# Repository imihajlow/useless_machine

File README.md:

# Useless machine

This project is an attempt to design a useless machine (the one that does nothing but turing off the switch) from scratch.
The reductor gears are designed to be 3d-printed.
The low-power controller can be reused for other small applications: it provides some GPIO pins, UART, and bidirectional motor driver.
The controller's power consumption is low enough to sustain on a CR2032 battery for more than 1.5 years in standby mode.

* mechanics/ - AutoCAD drawings of the mechanical part of the machine. This folder also contains the belt length calculation script.
* controller/ - the electronic part. Schematic drawing, PCB layout and gerber files for production.
* firmware/ - firmware for the controller. You need SDCC (http://sdcc.sourceforge.net) to compile.

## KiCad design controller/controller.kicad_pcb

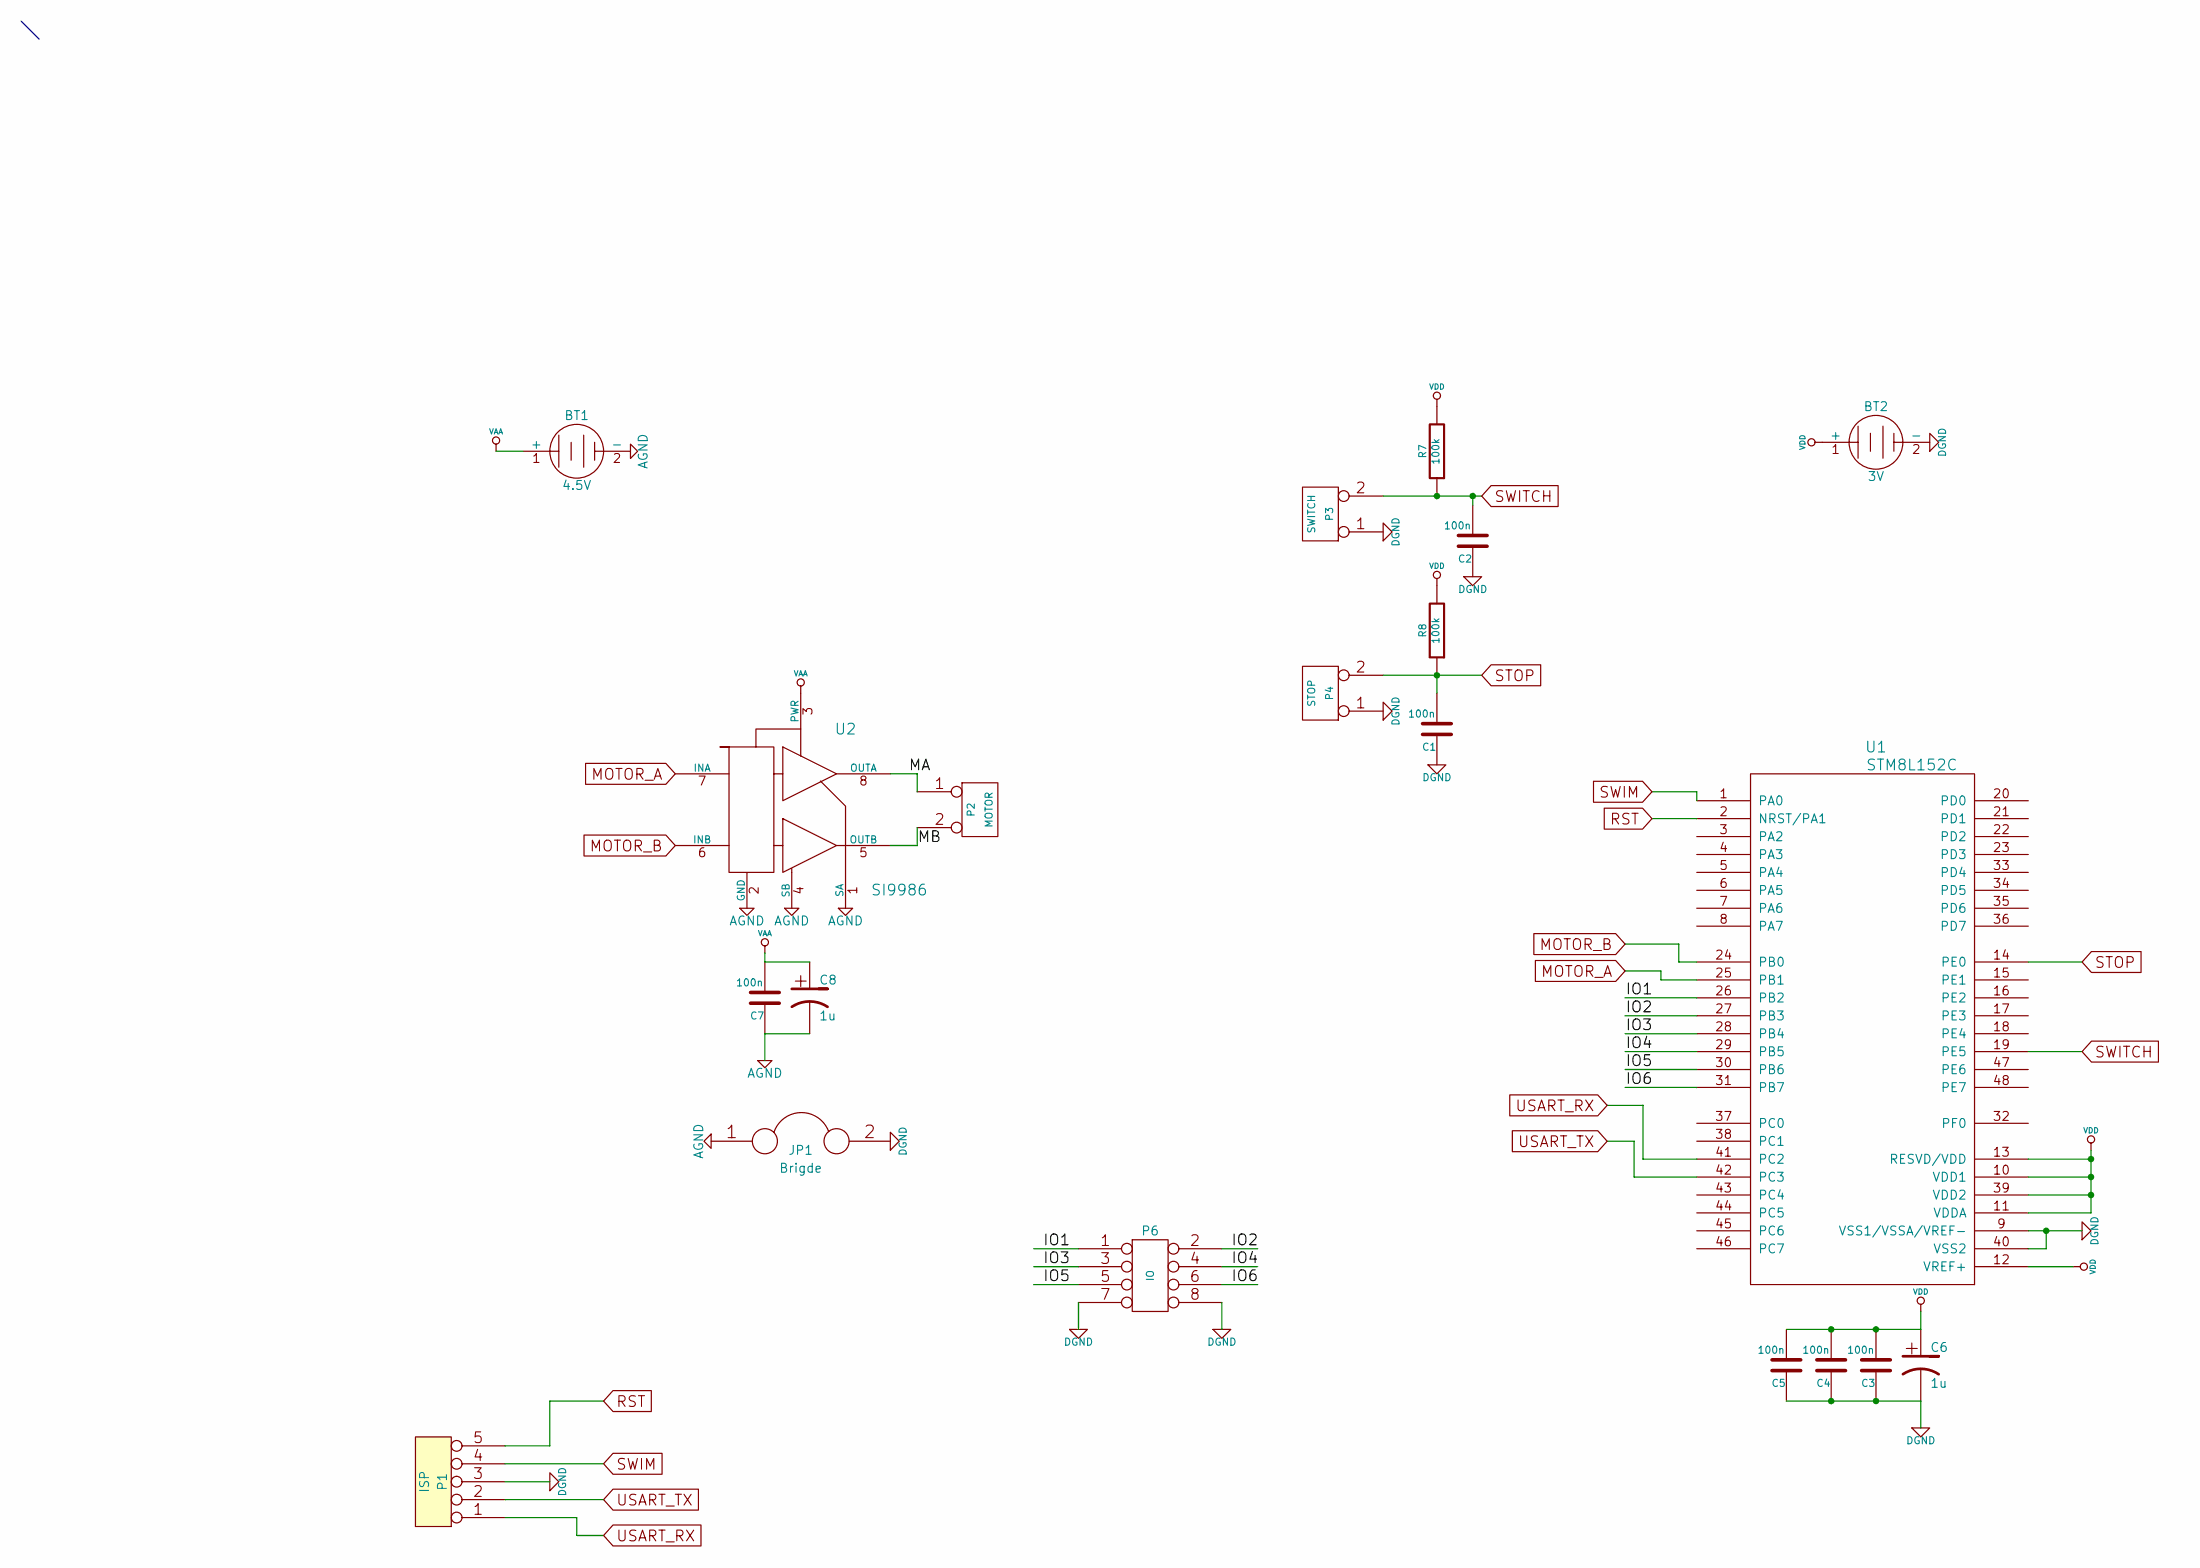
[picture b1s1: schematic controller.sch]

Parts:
BT1: 4.5V
BT2: 3V
C1, C2, C3, C4, C5, C7: 100n
C6, C8: 1u
JP1: Brigde
P1: ISP
P2: MOTOR
P3: SWITCH
P4: STOP
P6: IO
R7, R8: 100k
U1: STM8L152C
U2: SI9986

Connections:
/IO1: P6.1, U1.26 (PB2)
/IO2: P6.2, U1.27 (PB3)
/IO3: P6.3, U1.28 (PB4)
/IO4: P6.4, U1.29 (PB5)
/IO5: P6.5, U1.30 (PB6)
/IO6: P6.6, U1.31 (PB7)
/MA: P2.1, U2.8 (OUTA)
/MB: P2.2 (PM), U2.5 (OUTB)
AGND: BT1.2 (-), C7.1, C8.2, JP1.1, U2.1 (SA), U2.2 (GND), U2.4 (SB)
DGND: BT2.2 (-), C1.1, C2.1, C3.1, C4.1, C5.1, C6.2, JP1.2, P1.3, P3.1, P4.1, P6.7, P6.8, U1.9 (VSS1/VSSA/VREF-), U1.40 (VSS2)
MOTOR_A: U1.25 (PB1), U2.7 (INA)
MOTOR_B: U1.24 (PB0), U2.6 (INB)
RST: P1.5, U1.2 (NRST/PA1)
STOP: C1.2, P4.2 (PM), R8.1, U1.14 (PE0)
SWIM: P1.4, U1.1 (PA0)
SWITCH: C2.2, P3.2 (PM), R7.1, U1.19 (PE5)
USART_RX: P1.1, U1.41 (PC2)
USART_TX: P1.2, U1.42 (PC3)
VAA: BT1.1 (+), C7.2, C8.1, U2.3 (PWR)
VDD: BT2.1 (+), C3.2, C4.2, C5.2, C6.1, R7.2, R8.2, U1.10 (VDD1), U1.11 (VDDA), U1.12 (VREF+), U1.13 (RESVD/VDD), U1.39 (VDD2)

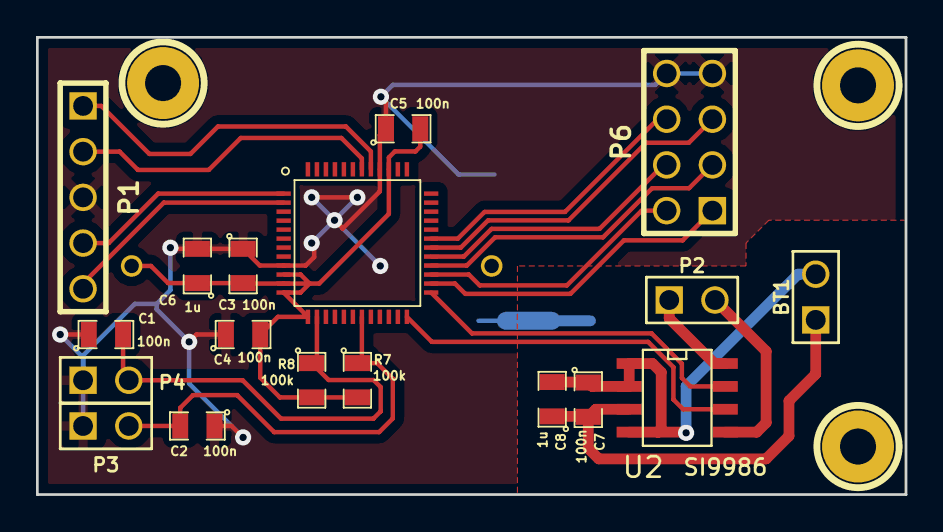
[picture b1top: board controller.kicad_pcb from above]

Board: 2 copper layers, 48.3 x 25.4 mm, 19 parts (1 on the bottom side), 20 nets.

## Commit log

2017-02-11 Firmware clean-up
2017-02-11 Removed sch/ directory with outdated simulation
2017-02-11 Moved mechanics drawings into a separate folder
2017-02-11 Removed outdated drawings
2017-02-11 Controller schemantic and PCB files added
2017-02-11 Moved belt calculation script
2017-02-11 README added.
2017-02-21 Added SVG layout of the box to be used by laser cutter.
